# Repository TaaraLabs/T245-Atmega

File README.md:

T245-Atmega
===========

Atmega 328 based open source controller for JBC T245 soldering iron

[Website](https://taaralabs.eu/sc1)

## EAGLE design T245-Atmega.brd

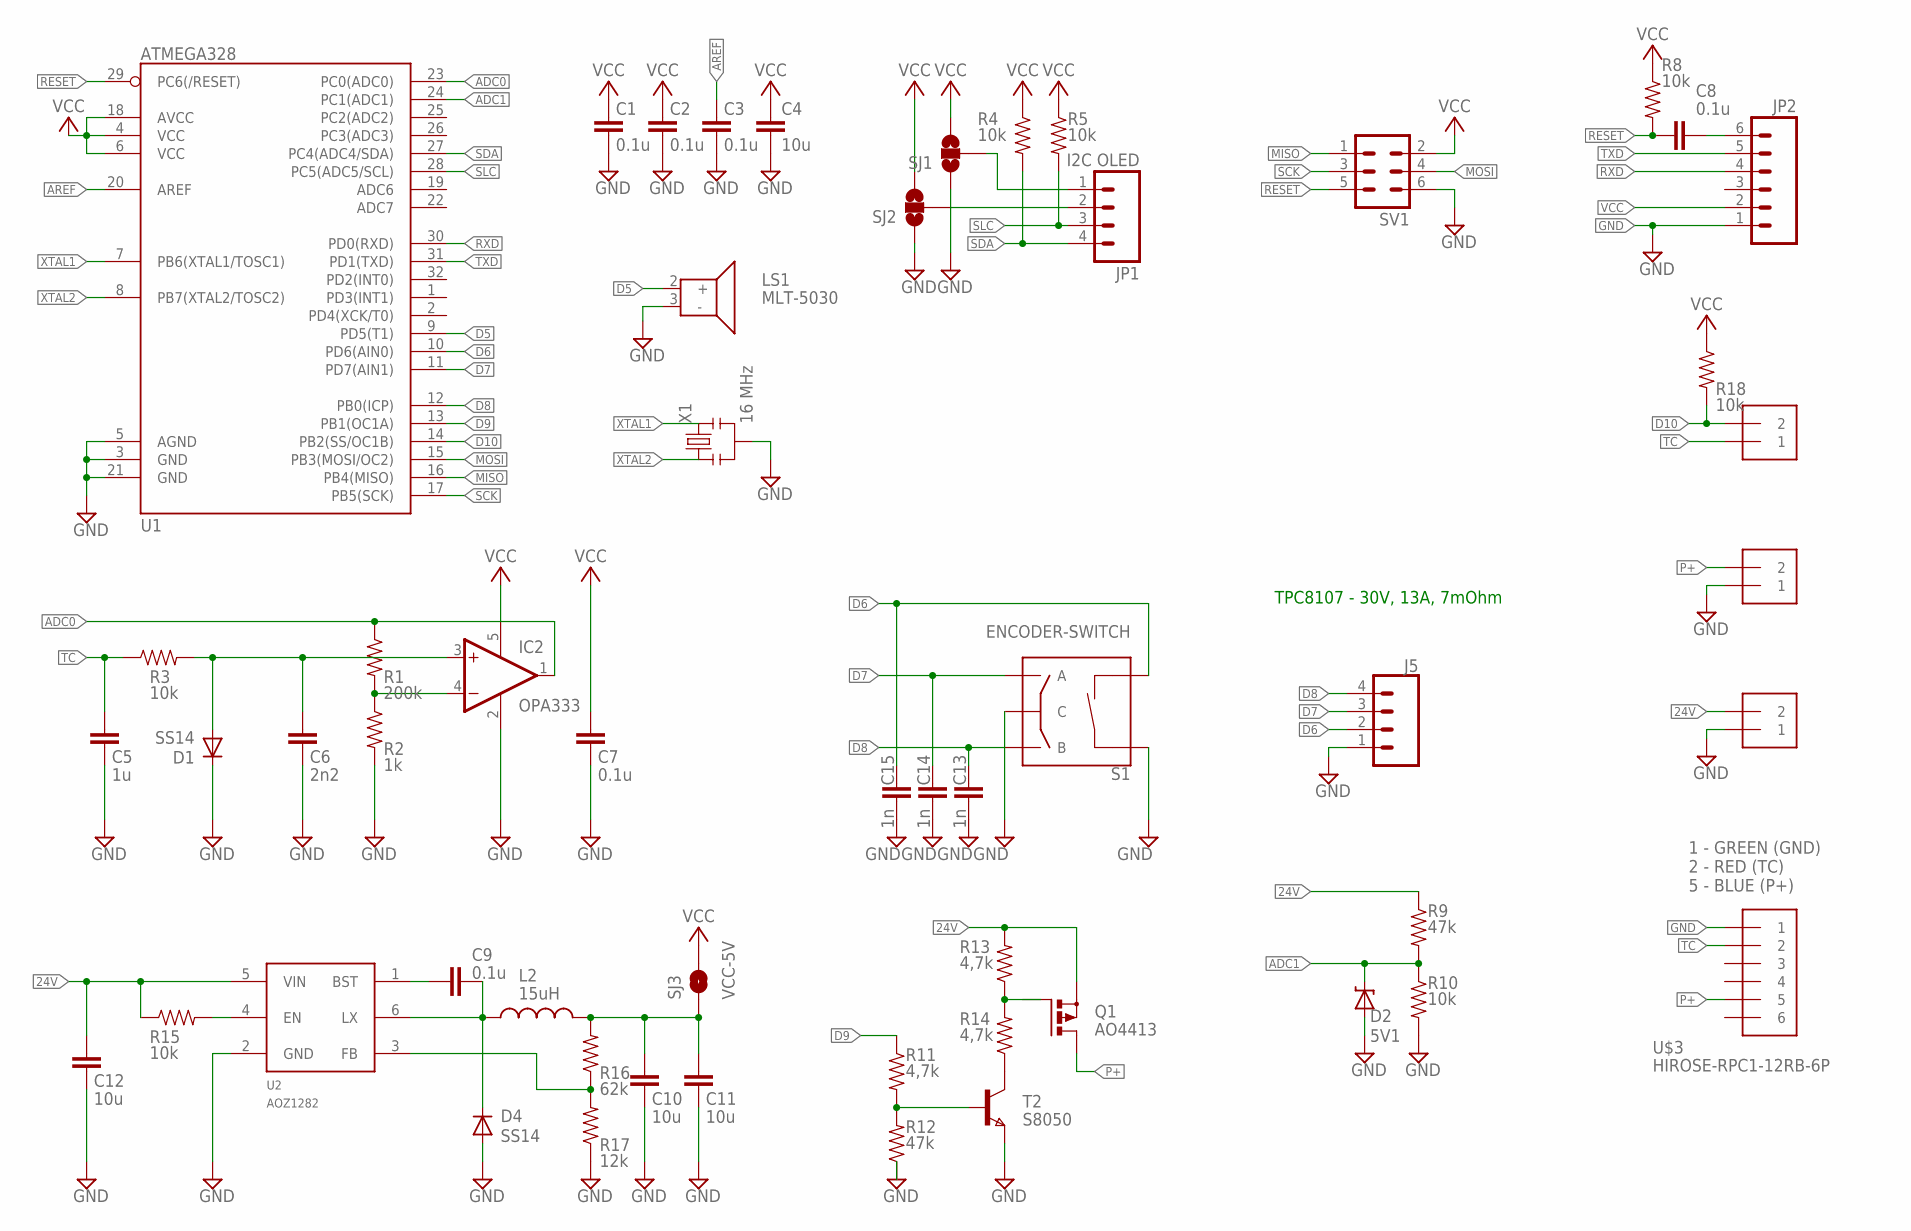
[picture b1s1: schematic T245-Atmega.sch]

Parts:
C1, C2, C3, C7, C8, C9: 0.1u; 0805
C4, C10, C11: 10u; 0805
C5: 1u; 0805
C6: 2n2; 0805
C12: 10u; 1210
C13, C14, C15: 1n; 0805
D1, D4: SS14; SOD-323F
D2: 5V1; SOD-323
IC2: OPA333; SOT23-5
J1: HEATER; 1X2-3.5MM
J3: Sensors; 1X2-3.5MM
J4: 24V; 1X2-3.5MM
J5: M04SMALL_DIAMETER; 1X04_SMALL_DIAMETER
JP1: I2C OLED; 1X04_SMALL_DIAMETER
JP2: M06SIP; 1X06
L2: 15uH; 1210
LS1: MLT-5030; SMT0540T7R
Q1: AO4413; SO-08
R1: 200k; 0805
R2: 1k; 0805
R3, R4, R5, R8, R10, R15, R18: 10k; 0805
R9, R12: 47k; 0805
R11, R13, R14: 4,7k; 0805
R16: 62k; 0805
R17: 12k; 0805
S1: ENCODER-SWITCH; ROTARY_ENC_PLAIN
SJ1: SOLDERJUMPER_2WAYPASTE1&2; SJ_3_PASTE1&2
SJ2: SOLDERJUMPER_2WAYPASTE2&3; SJ_3_PASTE2&3
SJ3: VCC-5V; SJ_2S-NOTRACE
SV1: MA03-2
T2: S8050; SOT-23-DOCU
U1: ATMEGA328; TQFP32-08
U2: AOZ1282; SOT23-6
U$3: HIROSE-RPC1-12RB-6P; HIROSER-PC1-12RB-6P
X1: 16 MHz; RESONATOR-SMD

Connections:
5V: C10.1, C11.1, L2.2, R16.2, SJ3.1
24V: C12.1, J4.2, Q1.1 (S), Q1.2 (S), Q1.3 (S), R9.1, R13.2, R15.1, U2.5 (VIN)
ADC0: IC2.1 (OUT), R1.1, U1.23 (PC0(ADC0))
ADC1: D2.1 (C), R9.2, R10.1, U1.24 (PC1(ADC1))
AREF: C3.1, U1.20 (AREF)
BASE: R11.2, R12.2, T2.3 (B)
BST: C9.1, U2.1 (BST)
COLLECTOR: R14.1, T2.1 (C)
D5: LS1.2 (+), U1.9 (PD5(T1))
D6: C15.2, J5.2, S1.SW-, U1.10 (PD6(AIN0))
D7: C14.2, J5.3, S1.A, U1.11 (PD7(AIN1))
D8: C13.2, J5.4, S1.B, U1.12 (PB0(ICP))
D9: R11.1, U1.13 (PB1(OC1A))
D10: J3.2, R18.2, U1.14 (PB2(SS/OC1B))
DTR: C8.2, JP2.6
EN: R15.2, U2.4 (EN)
FB: R16.1, R17.2, U2.3 (FB)
GATE: Q1.4 (G), R13.1, R14.2
GND: C1.2, C2.2, C3.2, C4.2, C5.2, C6.2, C7.2, C10.2, C11.2, C12.2, C13.1, C14.1, C15.1, D1.C, D2.2 (A), D4.A, IC2.2 (V-), J1.1, J4.1, J5.1, JP2.1, LS1.3 (-), R2.2, R10.2, R12.1, R17.1, S1.C, S1.SW+, SJ1.1, SJ2.1, SV1.6, T2.2 (E), U1.3 (GND), U1.5 (AGND), U1.21 (GND), U2.2 (GND), U$3.P$1 (1), X1.2
IN+: C6.1, D1.A, IC2.3 (+IN), R3.2
IN-: IC2.4 (-IN), R1.2, R2.1
LX: C9.2, D4.C, L2.1, U2.6 (LX)
MISO: SV1.1, U1.16 (PB4(MISO))
MOSI: SV1.4, U1.15 (PB3(MOSI/OC2))
unnamed: JP1.2, SJ2.2
unnamed: JP1.1, SJ1.2
P+: J1.2, Q1.5 (D), Q1.6 (D), Q1.7 (D), Q1.8 (D), U$3.P$5 (5)
RESET: C8.1, R8.2, SV1.5, U1.29 (PC6(/RESET))
RXD: JP2.4, U1.30 (PD0(RXD))
SCK: SV1.3, U1.17 (PB5(SCK))
SDA: JP1.4, R4.2, U1.27 (PC4(ADC4/SDA))
SLC: JP1.3, R5.2, U1.28 (PC5(ADC5/SCL))
TC: C5.1, J3.1, R3.1, U$3.P$2 (2)
TXD: JP2.5, U1.31 (PD1(TXD))
VCC: C1.1, C2.1, C4.1, C7.1, IC2.5 (V+), JP2.2, R4.1, R5.1, R8.1, R18.1, SJ1.3, SJ2.3, SJ3.2, SV1.2, U1.4 (VCC), U1.6 (VCC), U1.18 (AVCC)
XTAL1: U1.7 (PB6(XTAL1/TOSC1)), X1.3
XTAL2: U1.8 (PB7(XTAL2/TOSC2)), X1.1

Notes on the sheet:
1 - GREEN (GND) 2 - RED (TC) 5 - BLUE (P+)
TPC8107 - 30V, 13A, 7mOhm

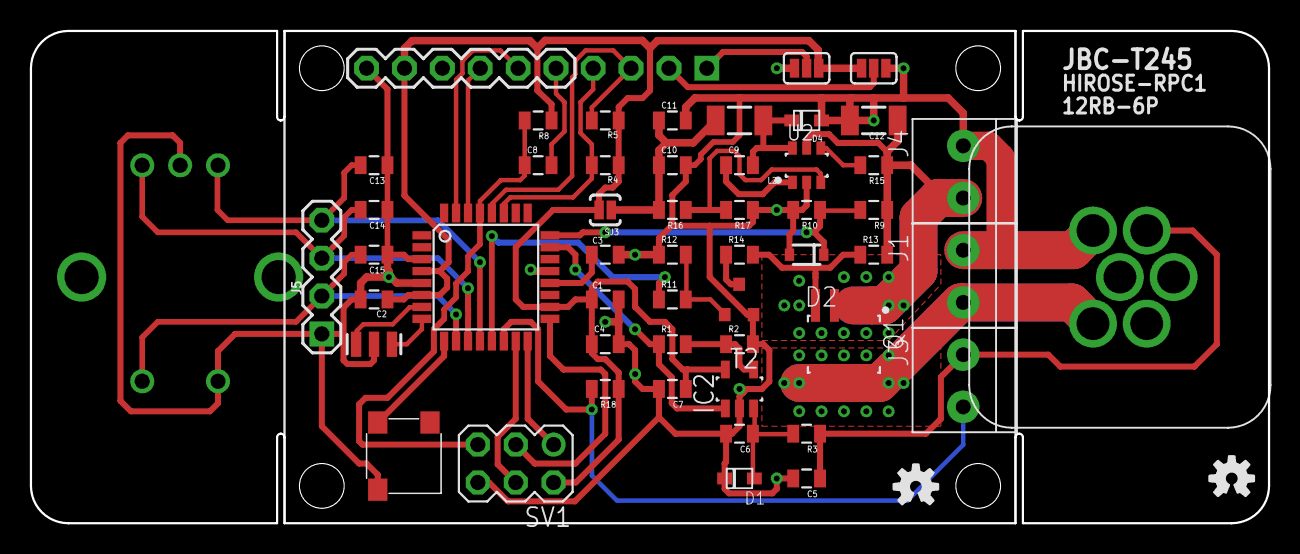
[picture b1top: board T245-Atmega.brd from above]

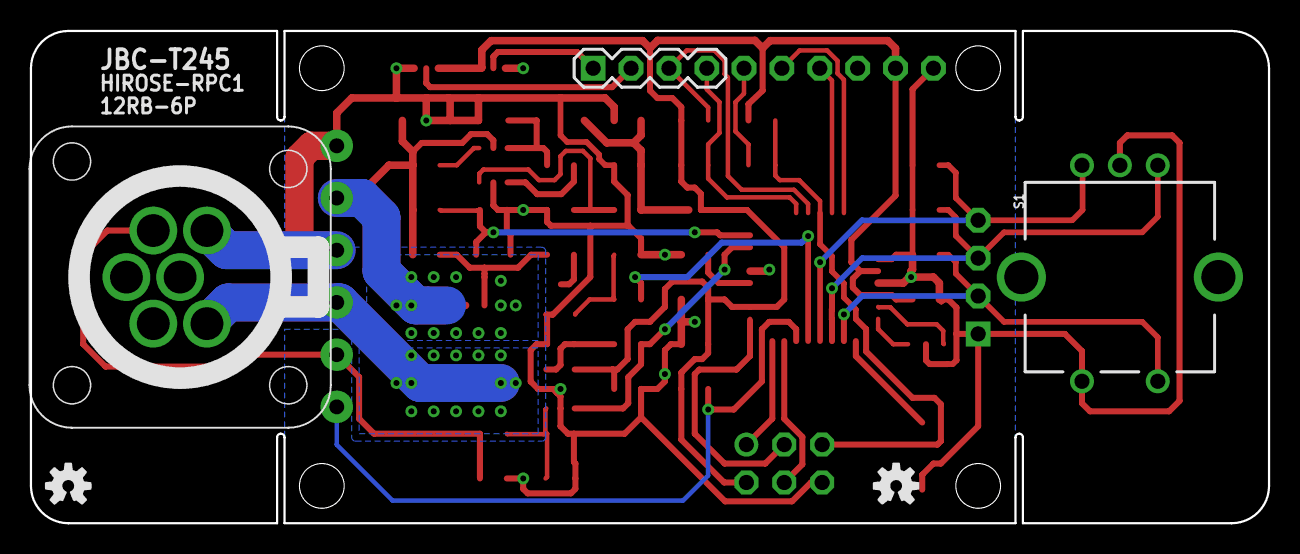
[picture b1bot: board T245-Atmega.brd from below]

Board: 2 copper layers, 83.0 x 33.0 mm, 58 parts (5 on the bottom side), 37 nets.

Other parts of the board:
U$1, U$2, U$4, U$5: OSHW-LOGO-S

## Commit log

2023-02-14 first upload
2023-02-14 pictures added
2023-02-14 README updated
2023-02-14 PCB image modified
2023-02-14 cosmetic modifications

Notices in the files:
parts and their libraries:
SparkFun-Aesthetics: Licensing: CC v3.0 Share-Alike You are welcome to use this library for commercial purposes.
SparkFun-Aesthetics: Licensing: Creative Commons ShareAlike 4.0 International - https://creativecommons.org/licenses/by-sa/4.0
